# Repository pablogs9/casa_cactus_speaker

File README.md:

# Casa Cactus Speaker

Repository for a project featuring an ESP32-S3 and an I2S Class D amplifier for audio playback.

Created for a Makespace Madrid session to demonstrate a complete PCB design workflow, from schematic to JLCPCB fabrication.

**Companion slides: [here](https://docs.google.com/presentation/d/1glYFRo9XCKRI-qDjp1DA8M3mJohLk-lrxx0JoBPsboM/edit#slide=id.p)**

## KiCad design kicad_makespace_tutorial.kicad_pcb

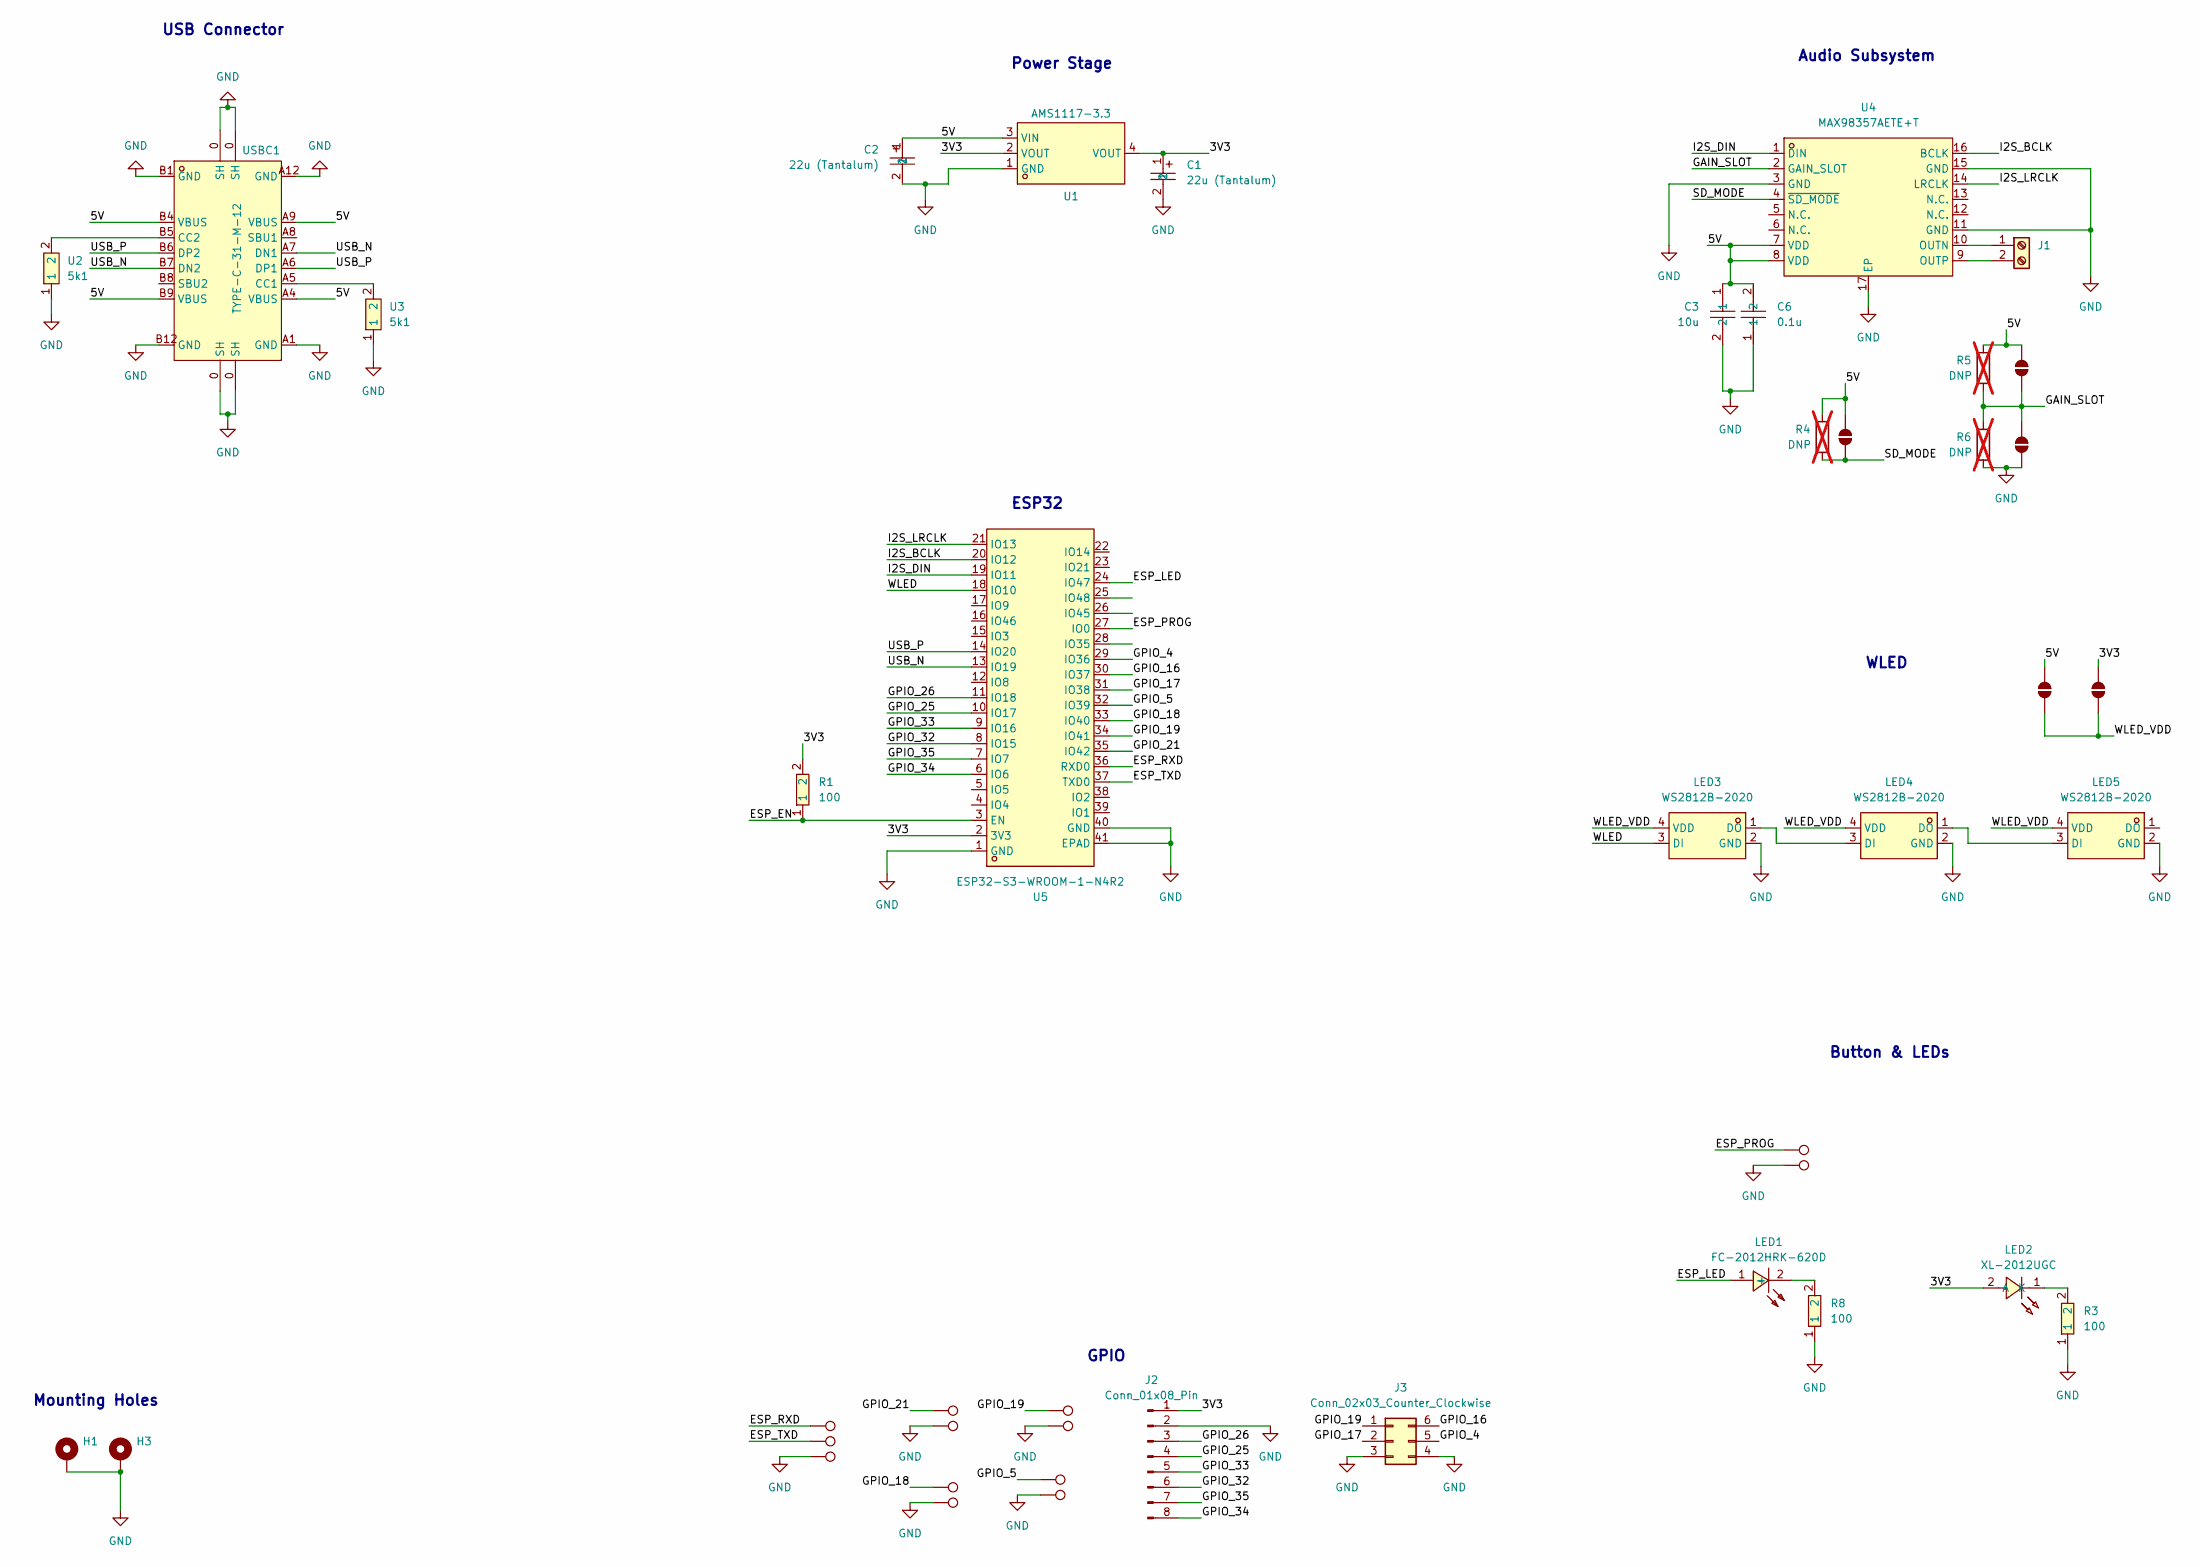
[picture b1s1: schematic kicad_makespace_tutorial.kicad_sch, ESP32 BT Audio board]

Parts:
C1, C2: 22u (Tantalum); CASE-A_3216; LCSC Part C129272
C3: 10u; C0805; LCSC Part C15850
C6: 0.1u; C0805; LCSC Part C49678
H1, H3: MountingHole_Pad_MP; MountingHole_2.7mm_M2.5_DIN965_Pad
J1: Screw_Terminal_01x02; CONN-TH_2P-P5.00_WJ128V-5.0-2P
J2: Conn_01x08_Pin; PinHeader_1x08_P1.27mm_Vertical_SMD_Pin1Right
J3: Conn_02x03_Counter_Clockwise; PinHeader_2x03_P2.00mm_Vertical
JP1, JP2, JP3, JP4, JP5: SolderJumper_2_Open; SolderJumper-2_P1.3mm_Open_TrianglePad1.0x1.5mm
LED1: FC-2012HRK-620D; LED0805-R-RD; LCSC Part C84256
LED2: XL-2012UGC; LED0805-RD_GREEN; LCSC Part C965815
LED3, LED4, LED5: WS2812B-2020; LED-SMD_4P-L2.0-W2.0-TL_WS2812B-2020; LCSC Part C965555
R1, R3, R8: 100; R0805; LCSC Part C17408
R4, R5, R6: DNP; R_0805_2012Metric_Pad1.20x1.40mm_HandSolder; not fitted
TP1, TP2, TP3, TP4, TP5, TP6, TP12, TP13, TP15, TP16, TP17, TP18, TP19: TestPoint; TestPoint_Pad_D1.0mm
U1: AMS1117-3.3; SOT-223-3_L6.5-W3.4-P2.30-LS7.0-BR; LCSC Part C6186
U2, U3: 5k1; R0805; LCSC Part C2930296
U4: MAX98357AETE+T; TQFN-16_L3.0-W3.0-P0.50-BL-EP1.5; LCSC Part C910544
U5: ESP32-S3-WROOM-1-N4R2; WIRELM-SMD_ESP32-S3-WROOM-1; LCSC Part C2913203
USBC1: TYPE-C-31-M-12; USB-C_SMD-TYPE-C-31-M-12; LCSC Part C165948

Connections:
/3V3: C1.1, J2.1, JP5.2 (B), LED2.2 (A), R1.2, U1.2 (VOUT), U1.4 (VOUT), U5.2 (3V3)
/5V: C2.1, C3.1, C6.2, JP1.2 (B), JP3.2 (B), JP4.2 (B), R4.1, R5.1, U1.3 (VIN), U4.7 (VDD), U4.8 (VDD), USBC1.A4 (VBUS), USBC1.A9 (VBUS), USBC1.B4 (VBUS), USBC1.B9 (VBUS)
/ESP_EN: R1.1, U5.3 (EN)
/ESP_LED: LED1.1 (+), U5.24 (IO47)
/ESP_PROG: TP18.1, U5.27 (IO0)
/ESP_RXD: TP15.1, U5.36 (RXD0)
/ESP_TXD: TP16.1, U5.37 (TXD0)
/GAIN_SLOT: JP2.2 (B), JP3.1 (A), R5.2, R6.1, U4.2 (GAIN_SLOT)
/GPIO_4: J3.5, U5.29 (IO36)
/GPIO_5: TP12.1, U5.32 (IO39)
/GPIO_16: J3.6, U5.30 (IO37)
/GPIO_17: J3.2, U5.31 (IO38)
/GPIO_18: TP5.1, U5.33 (IO40)
/GPIO_19: J3.1, TP3.1, U5.34 (IO41)
/GPIO_21: TP2.1, U5.35 (IO42)
/GPIO_25: J2.4, U5.10 (IO17)
/GPIO_26: J2.3, U5.11 (IO18)
/GPIO_32: J2.6, U5.8 (IO15)
/GPIO_33: J2.5, U5.9 (IO16)
/GPIO_34: J2.8, U5.6 (IO6)
/GPIO_35: J2.7, U5.7 (IO7)
/I2S_BCLK: U4.16 (BCLK), U5.20 (IO12)
/I2S_DIN: U4.1 (DIN), U5.19 (IO11)
/I2S_LRCLK: U4.14 (LRCLK), U5.21 (IO13)
/SD_MODE: JP1.1 (A), R4.2, U4.4 (~SD_MODE)
/USB_N: U5.13 (IO19), USBC1.A7 (DN1), USBC1.B7 (DN2)
/USB_P: U5.14 (IO20), USBC1.A6 (DP1), USBC1.B6 (DP2)
/WLED: LED3.3 (DI), U5.18 (IO10)
/WLED_VDD: JP4.1 (A), JP5.1 (A), LED3.4 (VDD), LED4.4 (VDD), LED5.4 (VDD)
GND: C1.2, C2.2, C3.2, C6.1, H1.MP, H3.MP, J2.2, J3.3, J3.4, JP2.1 (A), LED3.2 (GND), LED4.2 (GND), LED5.2 (GND), R3.1, R6.2, R8.1, TP1.1, TP4.1, TP6.1, TP13.1, TP17.1, TP19.1, U1.1 (GND), U2.1, U3.1, U4.3 (GND), U4.11 (GND), U4.15 (GND), U4.17 (EP), U5.1 (GND), U5.40 (GND), U5.41 (EPAD), USBC1.0 (SH), USBC1.A1 (GND), USBC1.A12 (GND), USBC1.B1 (GND), USBC1.B12 (GND)
unnamed: J1.1, U4.10 (OUTN)
unnamed: J1.2, U4.9 (OUTP)
unnamed: LED1.2 (-), R8.2
unnamed: LED2.1 (K), R3.2
unnamed: LED3.1 (DO), LED4.3 (DI)
unnamed: LED4.1 (DO), LED5.3 (DI)
unnamed: U3.2, USBC1.A5 (CC1)
unnamed: U2.2, USBC1.B5 (CC2)

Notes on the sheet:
Button & LEDs
Mounting Holes
Power Stage
GPIO
Audio Subsystem
ESP32
WLED
USB Connector

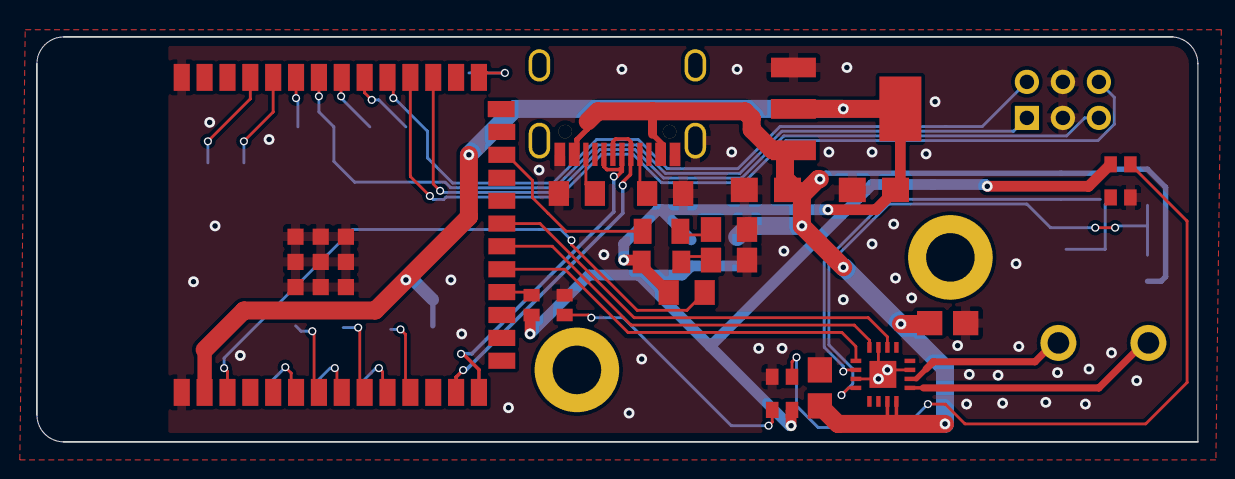
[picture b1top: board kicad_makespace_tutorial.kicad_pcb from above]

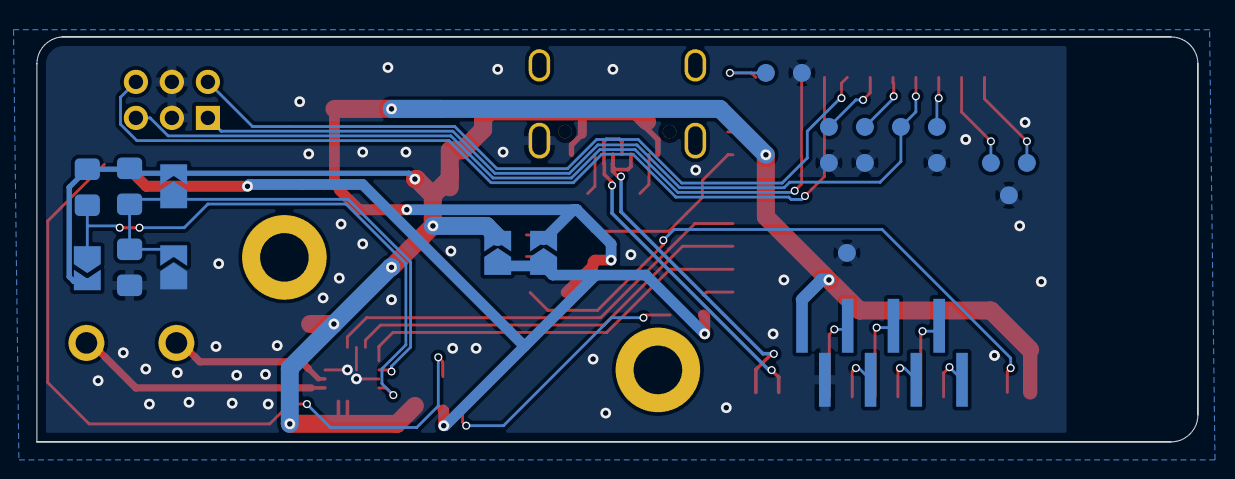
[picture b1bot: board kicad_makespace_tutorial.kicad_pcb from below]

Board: 2 copper layers, 64.5 x 22.5 mm, 44 parts (22 on the bottom side), 38 nets.

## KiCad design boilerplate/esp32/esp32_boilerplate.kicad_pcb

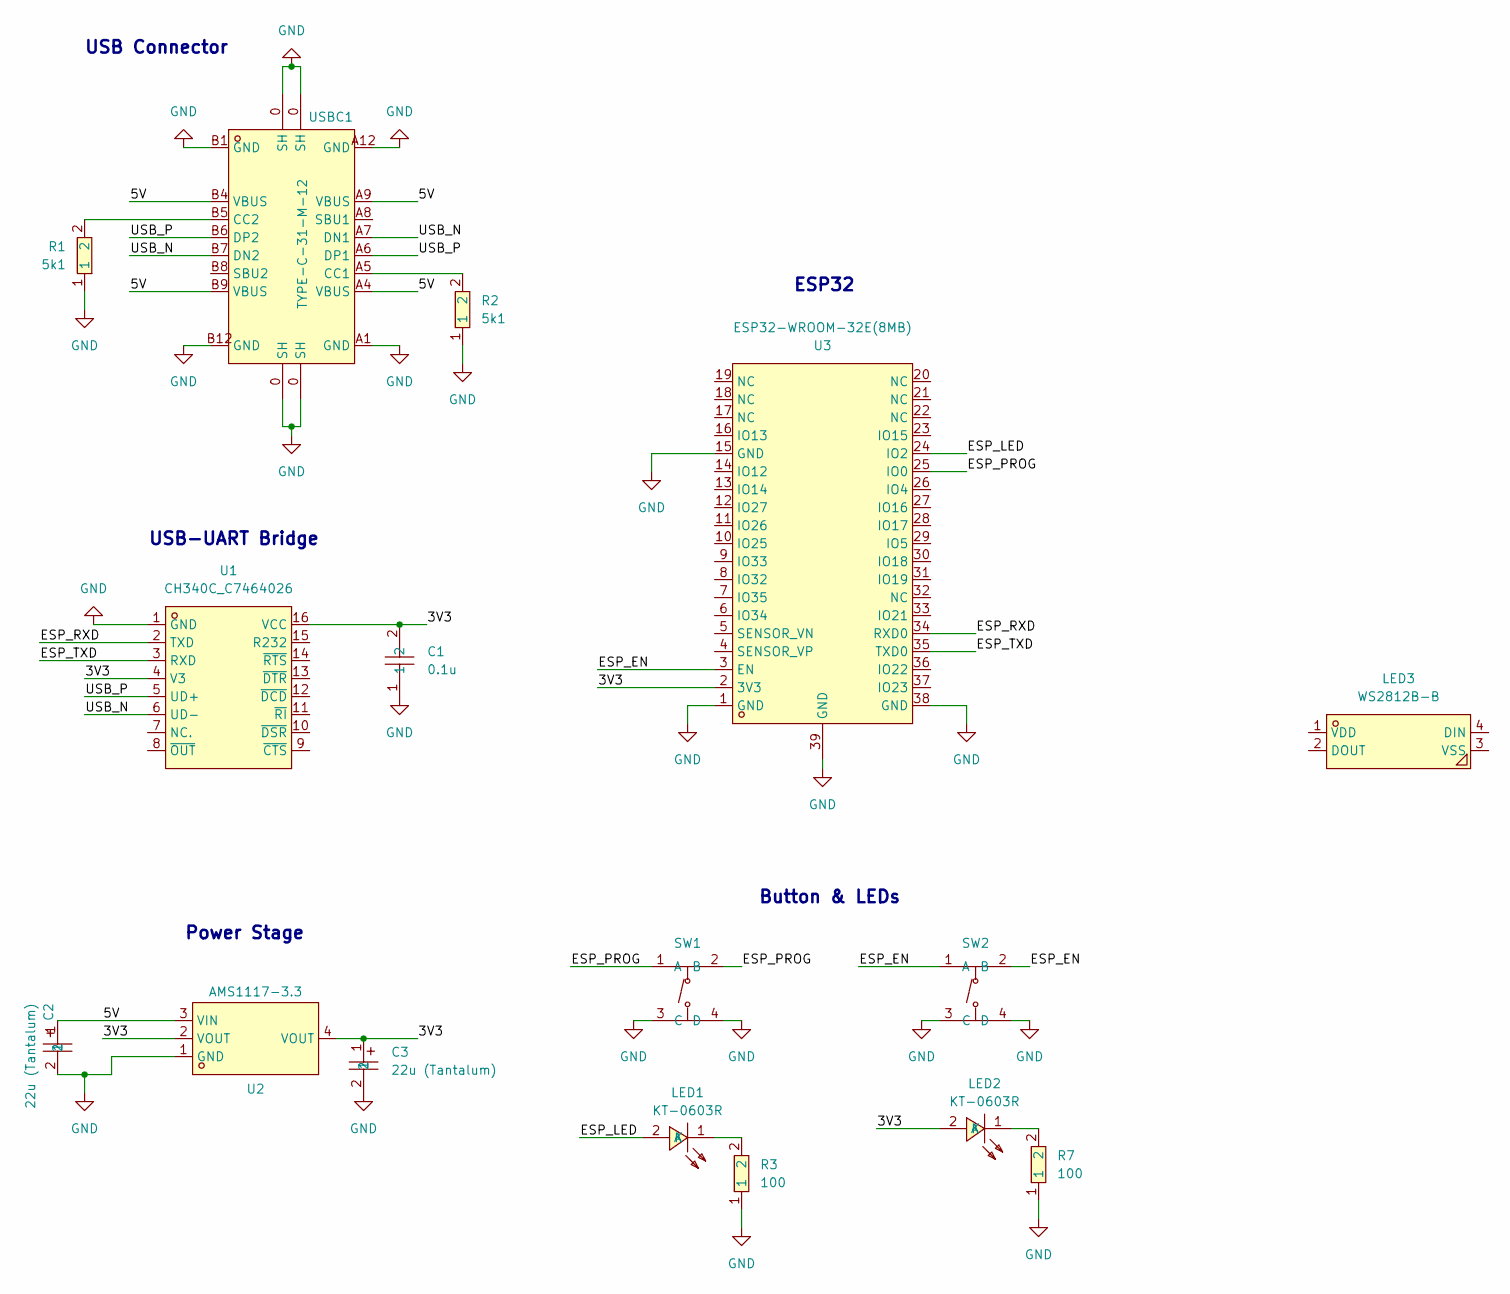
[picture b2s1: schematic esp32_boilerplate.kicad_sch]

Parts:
C1: 0.1u; C0603; LCSC Part C14663
C2, C3: 22u (Tantalum); CASE-A_3216; LCSC Part C129272
LED1, LED2: KT-0603R; LED0603-RD; LCSC Part C2286
LED3: WS2812B-B; LED-SMD_4P-L5.0-W5.0-BL_TC5050RGB; LCSC Part C114586
R1, R2: 5k1; R0603; LCSC Part C23186
R3, R7: 100; R0603; LCSC Part C22775
SW1, SW2: TS-1187A-B-A-B; SW-SMD_4P-L5.1-W5.1-P3.70-LS6.5-TL_H1.5; LCSC Part C318884
U1: CH340C_C7464026; SOP-16_L10.0-W3.9-P1.27-LS6.0-BL; LCSC Part C7464026
U2: AMS1117-3.3; SOT-223-3_L6.5-W3.4-P2.30-LS7.0-BR; LCSC Part C6186
U3: ESP32-WROOM-32E(8MB); WIFI-SMD_ESP32-WROOM-32E; LCSC Part C701342
USBC1: TYPE-C-31-M-12; USB-C_SMD-TYPE-C-31-M-12; LCSC Part C165948

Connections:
/3V3: C1.2, C3.1, LED2.2 (A), U1.4 (V3), U1.16 (VCC), U2.2 (VOUT), U2.4 (VOUT), U3.2 (3V3)
/5V: C2.1, U2.3 (VIN), USBC1.A4 (VBUS), USBC1.A9 (VBUS), USBC1.B4 (VBUS), USBC1.B9 (VBUS)
/ESP_EN: SW2.1 (A), SW2.2 (B), U3.3 (EN)
/ESP_LED: LED1.2 (A), U3.24 (IO2)
/ESP_PROG: SW1.1 (A), SW1.2 (B), U3.25 (IO0)
/ESP_RXD: U1.2 (TXD), U3.34 (RXD0)
/ESP_TXD: U1.3 (RXD), U3.35 (TXD0)
/USB_N: U1.6 (UD-), USBC1.A7 (DN1), USBC1.B7 (DN2)
/USB_P: U1.5 (UD+), USBC1.A6 (DP1), USBC1.B6 (DP2)
GND: C1.1, C2.2, C3.2, R1.1, R2.1, R3.1, R7.1, SW1.3 (C), SW1.4 (D), SW2.3 (C), SW2.4 (D), U1.1 (GND), U2.1 (GND), U3.1 (GND), U3.15 (GND), U3.38 (GND), U3.39 (GND), USBC1.0 (SH), USBC1.A1 (GND), USBC1.A12 (GND), USBC1.B1 (GND), USBC1.B12 (GND)
unnamed: LED1.1 (K), R3.2
unnamed: LED2.1 (K), R7.2
unnamed: R2.2, USBC1.A5 (CC1)
unnamed: R1.2, USBC1.B5 (CC2)

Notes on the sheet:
USB-UART Bridge
USB Connector
Power Stage
ESP32
Button & LEDs

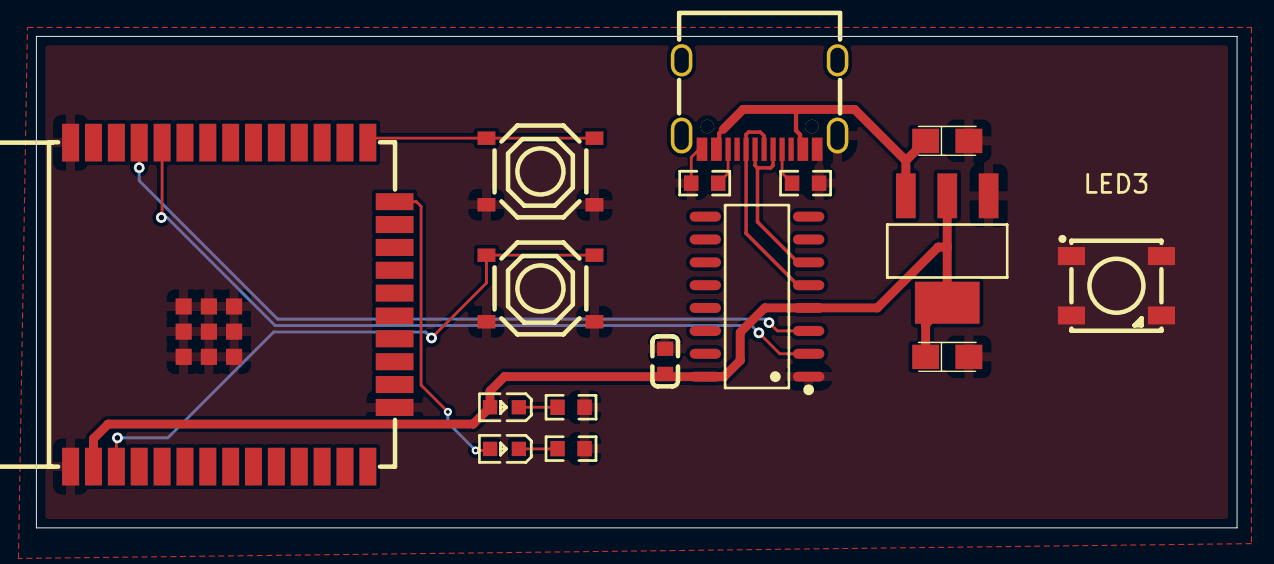
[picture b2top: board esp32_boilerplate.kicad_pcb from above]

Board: 2 copper layers, 66.7 x 27.3 mm, 16 parts (0 on the bottom side), 14 nets.

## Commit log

2025-01-18 Routed ESP32 boilerplate
2025-01-29 Bump Desing
2025-01-29 Add 3D model
2025-02-19 Final design
2025-03-30 Final Updates
2025-03-30 Remove boilerplate
2025-03-30 Rework folders
2025-03-30 Add firmware
2025-03-30 Add render image
2025-04-01 Initial efforts
2025-04-01 Reorder code
2025-04-02 New Linux code
2025-04-02 Working stage
2025-04-02 Ignore original folders
2025-04-02 Semiworking
2025-04-03 Minors
2025-05-07 Ongoing
2025-05-28 Build OK
2025-05-31 No audio
2025-05-31 saved UNDO information for reset changes and discarded files
